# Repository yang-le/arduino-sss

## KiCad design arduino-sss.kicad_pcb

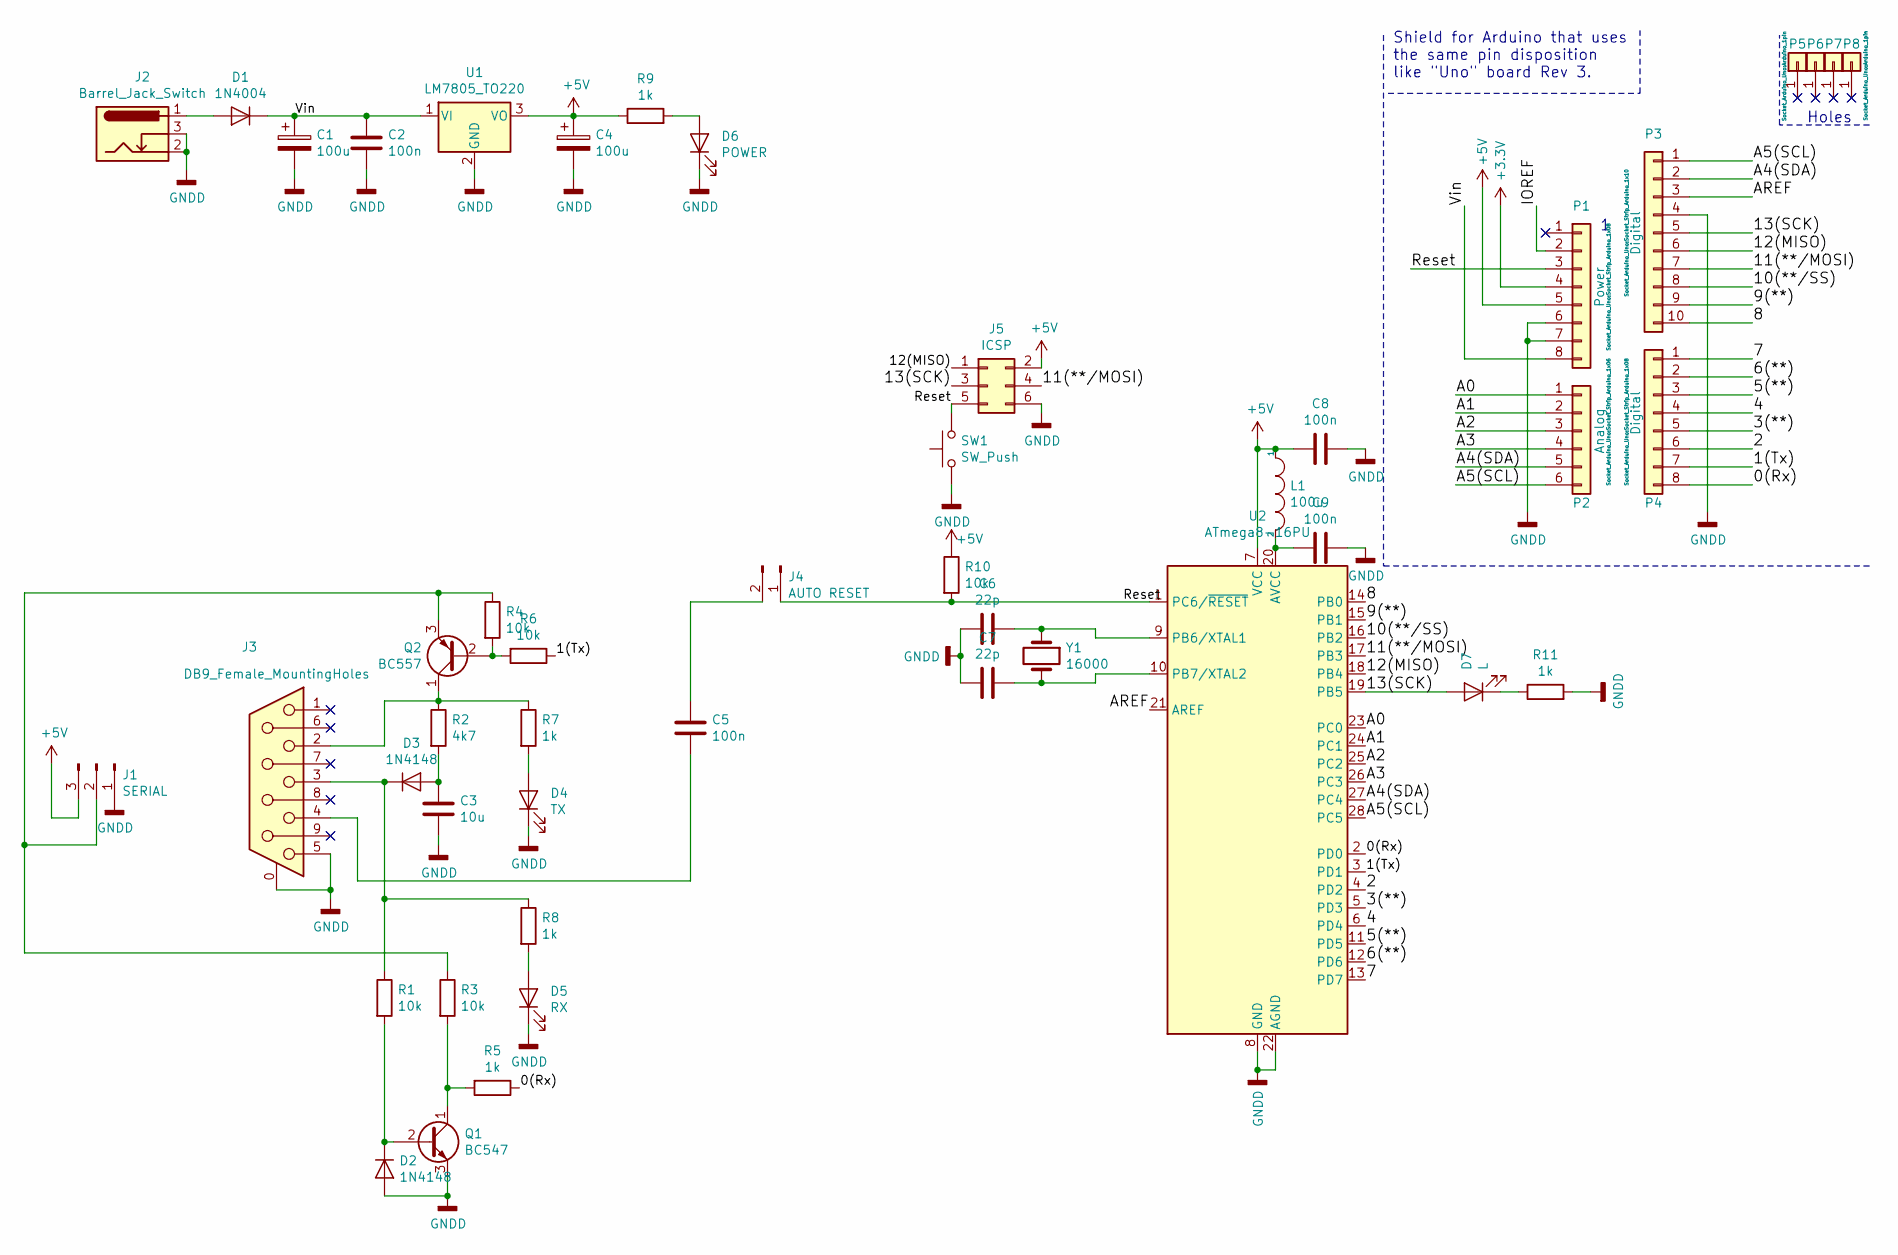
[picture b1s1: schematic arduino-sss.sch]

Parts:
C1, C4: 100u; C_Radial_D5.0mm_H7.0mm_P2.00mm
C2, C5, C8, C9: 100n; C_Disc_D8.0mm_W5.0mm_P7.50mm
C3: 10u; C_Radial_D4.0mm_H7.0mm_P1.50mm
C6, C7: 22p; C_Disc_D5.0mm_W2.5mm_P2.50mm
D1: 1N4004; D_DO-41_SOD81_P10.16mm_Horizontal
D2, D3: 1N4148; D_DO-35_SOD27_P10.16mm_Horizontal
D4: TX; LED_D3.0mm_Clear
D5: RX; LED_D3.0mm_Clear
D6: POWER; LED_D3.0mm_Clear
D7: L; LED_D3.0mm_Clear
J1: SERIAL; PinHeader_1x03_P2.54mm_Vertical
J2: Barrel_Jack_Switch; BarrelJack_Horizontal
J3: DB9_Female_MountingHoles; DSUB-9_Female_Horizontal_P2.77x2.84mm_EdgePinOffset7.70mm_H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
J4: AUTO RESET; PinHeader_1x02_P2.54mm_Vertical
J5: ICSP; PinHeader_2x03_P2.54mm_Vertical
L1: 100u; L_Axial_L12.0mm_D5.0mm_P15.24mm_Horizontal_Fastron_MISC
P1: Power; Socket_Strip_Arduino_1x08
P2: Analog; Socket_Strip_Arduino_1x06
P3: Digital; Socket_Strip_Arduino_1x10
P4: Digital; Socket_Strip_Arduino_1x08
P5, P6, P7, P8: CONN_01X01; Arduino_1pin
Q1: BC547; TO-92_Inline_Wide
Q2: BC557; TO-92_Inline_Wide
R1, R3, R4, R6, R10: 10k; R_Axial_DIN0207_L6.3mm_D2.5mm_P10.16mm_Horizontal
R2: 4k7; R_Axial_DIN0207_L6.3mm_D2.5mm_P10.16mm_Horizontal
R5, R7, R8, R9, R11: 1k; R_Axial_DIN0207_L6.3mm_D2.5mm_P10.16mm_Horizontal
SW1: SW_Push; SW_PUSH_6mm
U1: LM7805_TO220; TO-220-3_Horizontal_TabDown
U2: ATmega8-16PU; DIP-28_W7.62mm_Socket
Y1: 16000; Crystal_HC49-4H_Vertical

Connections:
+3V3: P1.4
+5V: C4.1, C8.2, J1.3, J5.2, L1.1, P1.5, R9.1, R10.1, U1.3 (VO), U2.7 (VCC)
/0(Rx): P4.8, R5.1, U2.2 (PD0)
/1(Tx): P4.7, R6.1, U2.3 (PD1)
/2: P4.6, U2.4 (PD2)
/3(**): P4.5, U2.5 (PD3)
/4: P4.4, U2.6 (PD4)
/5(**): P4.3, U2.11 (PD5)
/6(**): P4.2, U2.12 (PD6)
/7: P4.1, U2.13 (PD7)
/8: P3.10, U2.14 (PB0)
/9(**): P3.9, U2.15 (PB1)
/10(**/SS): P3.8, U2.16 (PB2)
/11(**/MOSI): J5.4, P3.7, U2.17 (PB3)
/12(MISO): J5.1, P3.6, U2.18 (PB4)
/13(SCK): D7.2 (A), J5.3, P3.5, U2.19 (PB5)
/A0: P2.1, U2.23 (PC0)
/A1: P2.2, U2.24 (PC1)
/A2: P2.3, U2.25 (PC2)
/A3: P2.4, U2.26 (PC3)
/A4(SDA): P2.5, P3.2, U2.27 (PC4)
/A5(SCL): P2.6, P3.1, U2.28 (PC5)
/AREF: P3.3, U2.21 (AREF)
/IOREF: P1.2
/Reset: J4.1, J5.5, P1.3, R10.2, SW1.2, U2.1 (PC6/~RESET)
/Vin: C1.1, C2.1, D1.1 (K), P1.8, U1.1 (VI)
GNDD: C1.2, C2.2, C3.2, C4.2, C6.2, C7.2, C8.1, C9.1, D2.2 (A), D4.1 (K), D5.1 (K), D6.1 (K), J1.1, J2.2, J2.3, J3.0 (PAD), J3.5, J5.6, P1.6, P1.7, P3.4, Q1.3 (E), R11.2, SW1.1, U1.2 (GND), U2.8 (GND), U2.22 (AGND)
unnamed: C3.1, D3.2 (A), R2.2
unnamed: C5.1, J4.2
unnamed: C5.2, J3.4
unnamed: C6.1, U2.9 (PB6/XTAL1), Y1.1
unnamed: C7.1, U2.10 (PB7/XTAL2), Y1.2
unnamed: C9.2, L1.2, U2.20 (AVCC)
unnamed: D1.2 (A), J2.1
unnamed: D2.1 (K), Q1.2 (B), R1.2
unnamed: D3.1 (K), J3.3, R1.1, R8.1
unnamed: D4.2 (A), R7.2
unnamed: D5.2 (A), R8.2
unnamed: D6.2 (A), R9.2
unnamed: D7.1 (K), R11.1
unnamed: J1.2, Q2.3 (E), R3.1, R4.1
unnamed: J3.2, Q2.1 (C), R2.1, R7.1
unnamed: Q1.1 (C), R3.2, R5.2
unnamed: Q2.2 (B), R4.2, R6.2

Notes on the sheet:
Holes
Shield for Arduino that uses the same pin disposition like "Uno" board Rev 3.

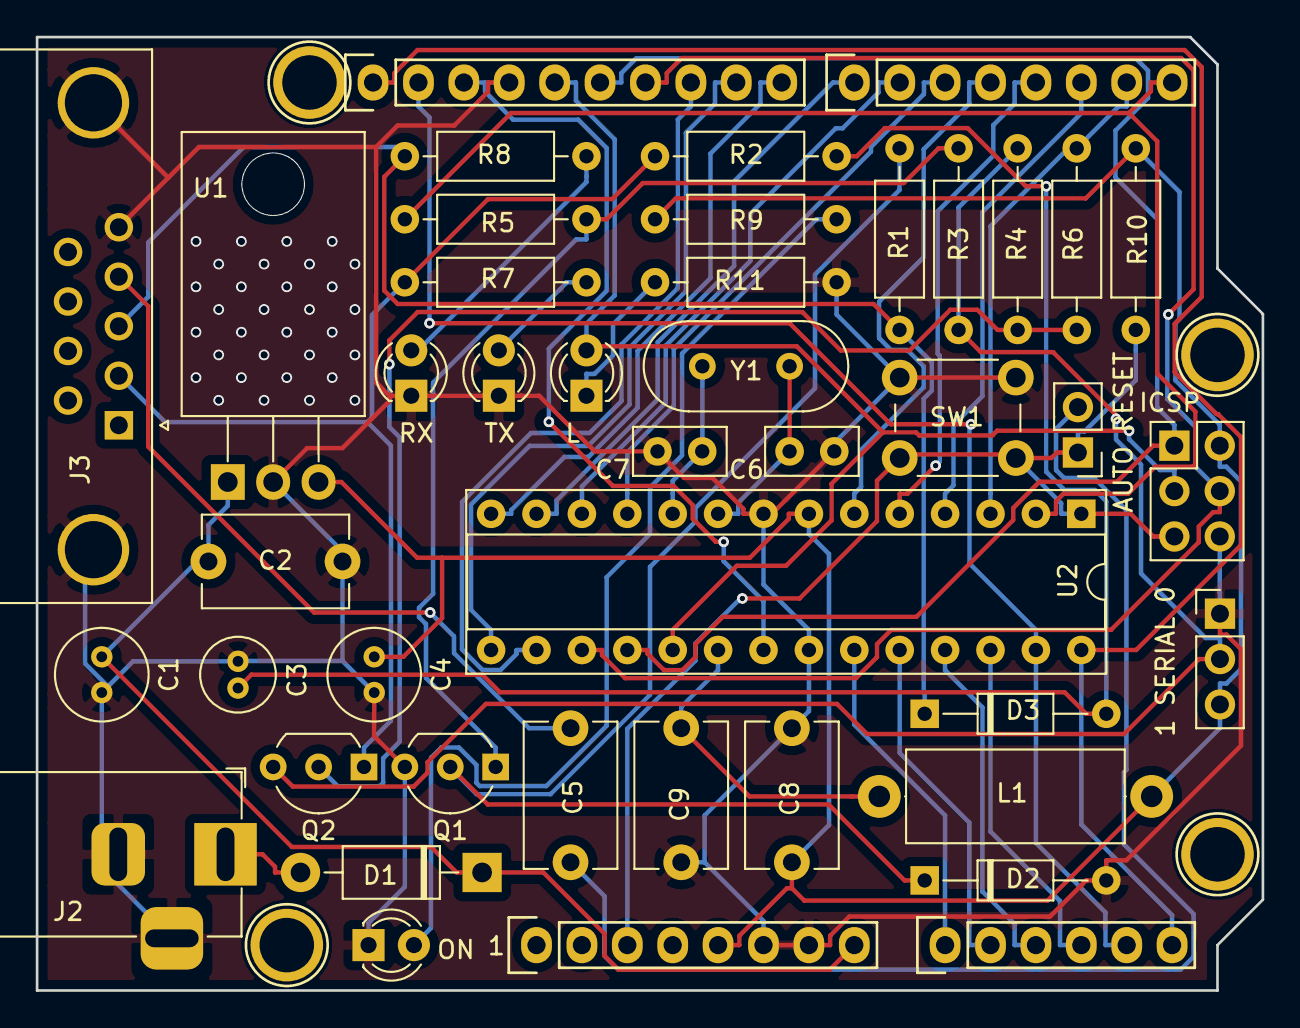
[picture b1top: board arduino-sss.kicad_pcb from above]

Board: 2 copper layers, 68.6 x 53.3 mm, 48 parts (1 on the bottom side), 42 nets.

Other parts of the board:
G2: LOGO

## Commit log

2019-10-03 ready to fab
2019-10-03 add version info
2019-10-04 update according to Real BOM
